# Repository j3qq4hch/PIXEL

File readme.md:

###PIXEL###
Pixel(yet another) is a dirt cheap 10W LED constant current driver with bells and whistles. 

Two common use scenarios are:

* LED LIGHTING with digital interface(smarthome applications)
* HUGE low-res LED screens with incredible brightness
 
 The device can operate in 2 modes:
 
* As modbus slave device over RS485 non-isolated inteface. This is relative slow mode which can be used for lighting automation systems or stage light control systems.  In this mode device's clock source is external quartz oscillator and it uses UART1 for communication. 
* As shift register. In this mode device operates like three daisy-chained 595 shift registers. In this mode device's clock source is internal RC(as frequency precision is not needed) and pins PF0 PF1 are used as GPIO(for LATCH and RESET signals). More, data clock is connected to PA4, data in is PA3, data out is PA9. So, data signal appears to be buffered by MCU. Clock, latch and reset signals are buffered by external ICs, so many PIXELs can be daisy-chained without concersn about bus integrity.  

Distinguishing between these modes is mostly a matter of proper connector selection, I think.  Mode selection may be done by adding solder joint to PA3 or PA9. These pins should be sampled right after MCU reset and one of the modes should be chosen then.

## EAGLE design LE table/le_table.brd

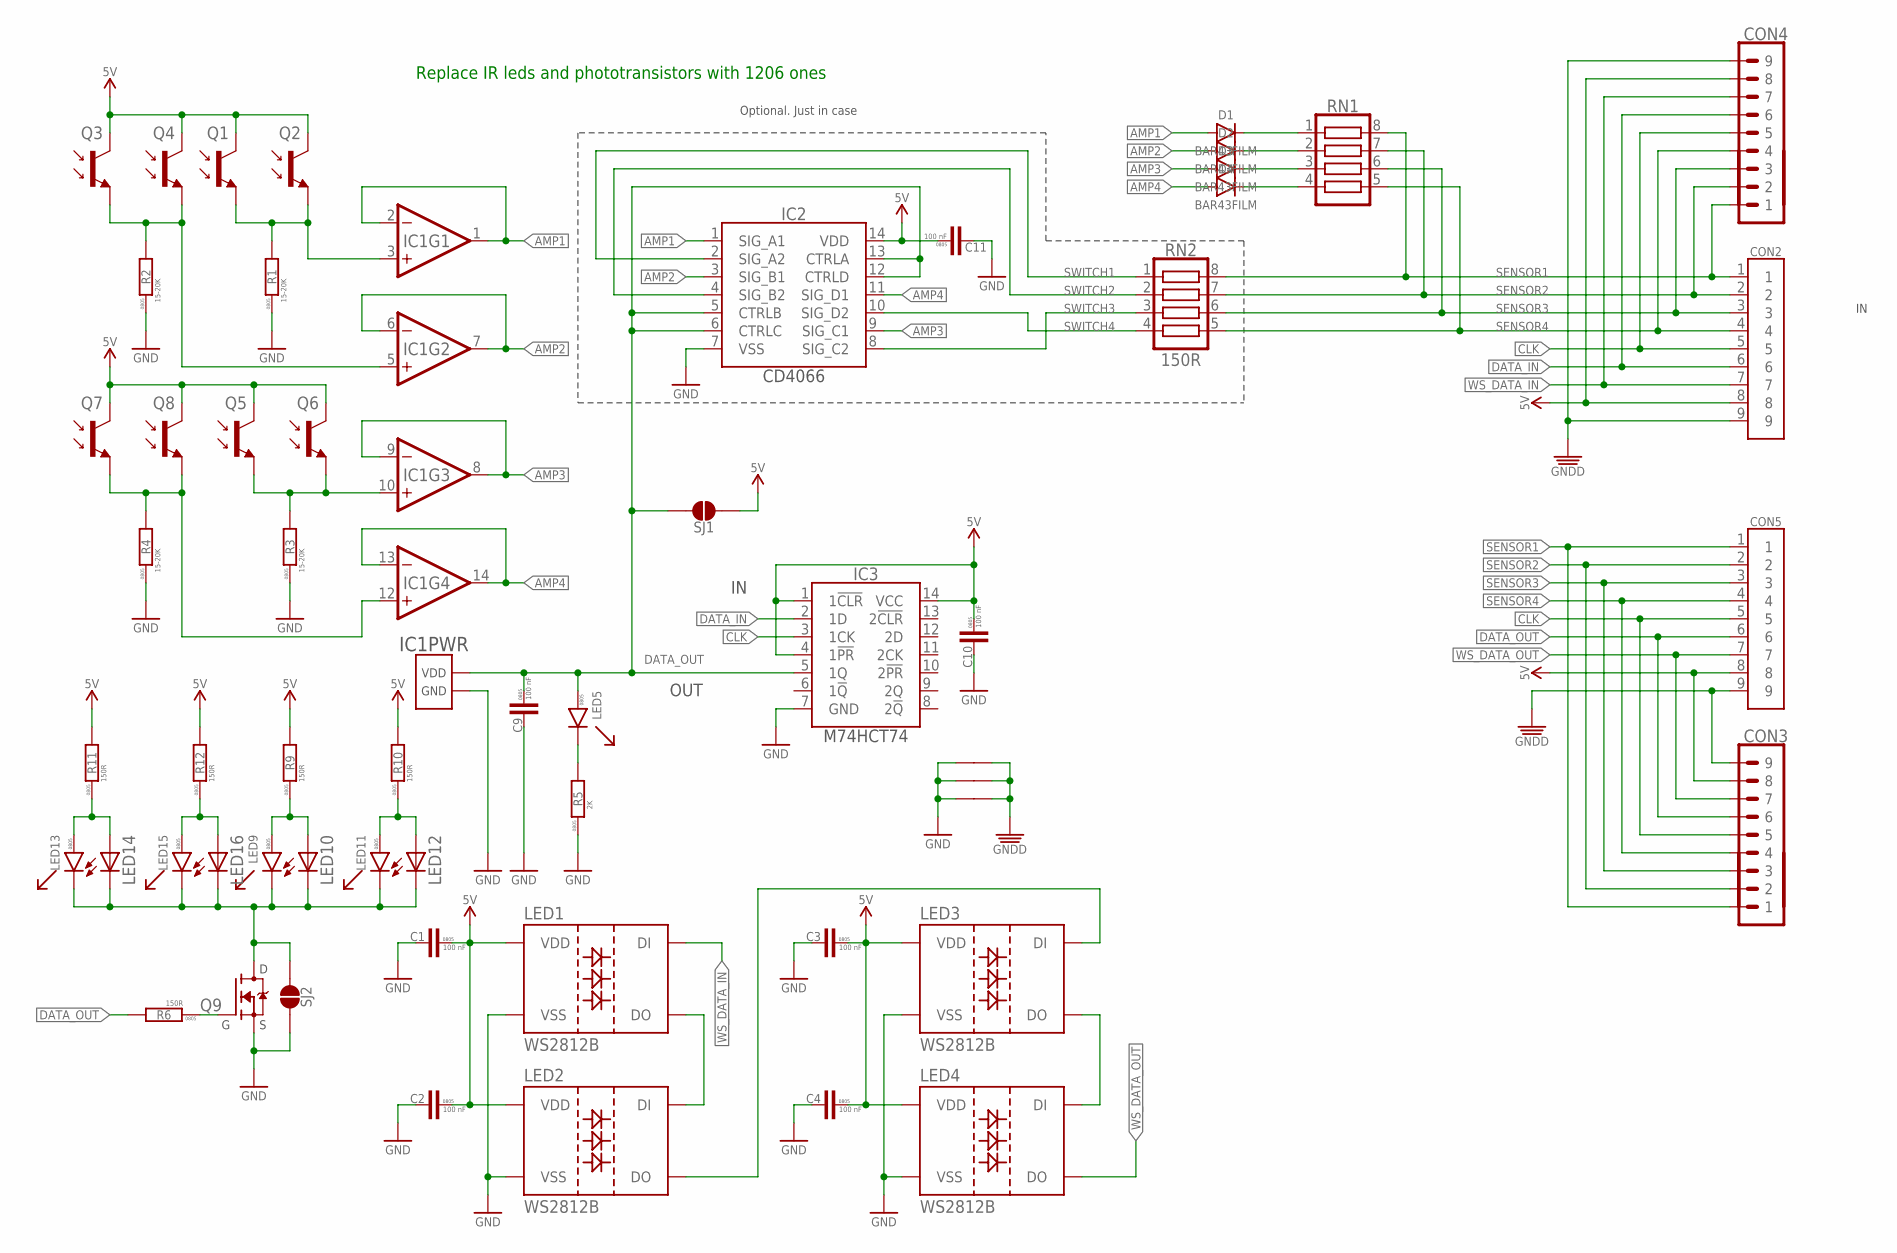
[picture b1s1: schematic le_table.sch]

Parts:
C1, C2, C3, C4, C9, C10, C11: 100 nF; C0805; FARNELL# 2496834
CON2, CON5: CONNECTOR
CON3, CON4: PINHEAD_1X09-2; 1X09-PTH_2
D1, D2, D3, D4: BAR43AFILM; SOT23-3
IC1: LM2902DT; SO-14
IC2: CD4066; SO-14
IC3: M74HCT74; SO-14
LED1, LED2, LED3, LED4: WS2812B
LED5, LED9, LED11, LED13, LED15: LED-0805; 0805_LED
LED10, LED12, LED14, LED16: LED-3MM
Q1, Q3, Q5, Q7: PHOTOTRANSISTOR-3MM; LED-3MM
Q2, Q4, Q6, Q8: PHOTOTRANSISTOR-0805; 0805
Q9: IRLML2502-SOT23; SOT23B-3
R1, R2, R3, R4: 15-20K; R0805
R5: 2K; R0805
R6, R9, R10, R11, R12: 150R; R0805
RN1: RESISTOR_ARRAY; CAT16-J4
RN2: 150R; CAT16-J4
SJ1, SJ2: SOLDER_JOINT; RES_0
U$3, U$6, U$7: CONNECTION

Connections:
AMP1: D1.1 (A), IC1.1 (OUT), IC1.2 (-IN), IC2.1 (SIG_A1)
AMP2: D2.1 (A), IC1.6 (-IN), IC1.7 (OUT), IC2.3 (SIG_B1)
AMP3: D3.1 (A), IC1.8 (OUT), IC1.9 (-IN), IC2.9 (SIG_C1)
AMP4: D4.1 (A), IC1.13 (-IN), IC1.14 (OUT), IC2.11 (SIG_D1)
CLK: CON2.5, CON3.5, CON4.5, CON5.5, IC3.3 (1CK)
DATA_IN: CON2.6, CON4.6, IC3.2 (1D)
DATA_OUT: C9.1, CON3.6, CON5.6, IC1.4 (VDD), IC2.5 (CTRLB), IC2.6 (CTRLC), IC2.12 (CTRLD), IC2.13 (CTRLA), IC3.5 (1Q), LED5.A, R6.2, SJ1.2
GND: C1.2, C2.2, C3.2, C4.2, C9.2, C10.2, C11.2, IC1.11 (GND), IC2.7 (VSS), IC3.7 (GND), LED1.3 (VSS), LED2.3 (VSS), LED3.3 (VSS), LED4.3 (VSS), Q9.2 (S), R1.1, R2.1, R3.1, R4.1, R5.1, SJ2.2, U$3.P$2, U$6.P$2, U$7.P$2
GNDD: CON2.9, CON3.9, CON4.9, CON5.9, U$3.P$1, U$6.P$1, U$7.P$1
unnamed: Q9.1 (G), R6.1
unnamed: LED5.C, R5.2
unnamed: LED1.2 (DO), LED2.4 (DI)
unnamed: LED2.2 (DO), LED3.4 (DI)
unnamed: LED3.2 (DO), LED4.4 (DI)
unnamed: LED11.A, LED12.A, R10.1
unnamed: LED13.A, LED14.A, R11.1
unnamed: LED9.A, LED10.A, R9.1
unnamed: LED15.A, LED16.A, R12.1
unnamed: D1.3 (C), RN1.1
unnamed: D2.3 (C), RN1.2
unnamed: D3.3 (C), RN1.3
unnamed: D4.3 (C), RN1.4
unnamed: LED9.C, LED10.K (C), LED11.C, LED12.K (C), LED13.C, LED14.K (C), LED15.C, LED16.K (C), Q9.3 (D), SJ2.1
SENS1: IC1.3 (+IN), Q1.K (E), Q2.2 (E), R1.2
SENS2: IC1.5 (+IN), Q3.K (E), Q4.2 (E), R2.2
SENS3: IC1.10 (+IN), Q5.K (E), Q6.2 (E), R3.2
SENS4: IC1.12 (+IN), Q7.K (E), Q8.2 (E), R4.2
SENSOR1: CON2.1, CON3.1, CON4.1, CON5.1, RN1.8, RN2.8
SENSOR2: CON2.2, CON3.2, CON4.2, CON5.2, RN1.7, RN2.7
SENSOR3: CON2.3, CON3.3, CON4.3, CON5.3, RN1.6, RN2.6
SENSOR4: CON2.4, CON3.4, CON4.4, CON5.4, RN1.5, RN2.5
SWITCH1: IC2.2 (SIG_A2), RN2.1
SWITCH2: IC2.4 (SIG_B2), RN2.2
SWITCH3: IC2.8 (SIG_C2), RN2.3
SWITCH4: IC2.10 (SIG_D2), RN2.4
VDD_5V: C1.1, C2.1, C3.1, C4.1, C10.1, C11.1, CON2.8, CON3.8, CON4.8, CON5.8, IC2.14 (VDD), IC3.1 (1!CLR), IC3.4 (1!PR), IC3.14 (VCC), LED1.1 (VDD), LED2.1 (VDD), LED3.1 (VDD), LED4.1 (VDD), Q1.A (C), Q2.1 (C), Q3.A (C), Q4.1 (C), Q5.A (C), Q6.1 (C), Q7.A (C), Q8.1 (C), R9.2, R10.2, R11.2, R12.2, SJ1.1
WS_DATA_IN: CON2.7, CON4.7, LED1.4 (DI)
WS_DATA_OUT: CON3.7, CON5.7, LED4.2 (DO)

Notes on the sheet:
OUT
Optional. Just in case
Replace IR leds and phototransistors with 1206 ones

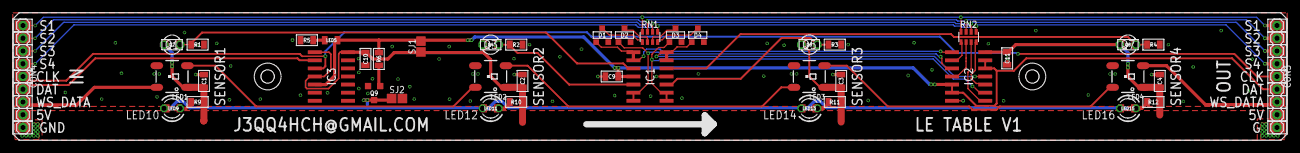
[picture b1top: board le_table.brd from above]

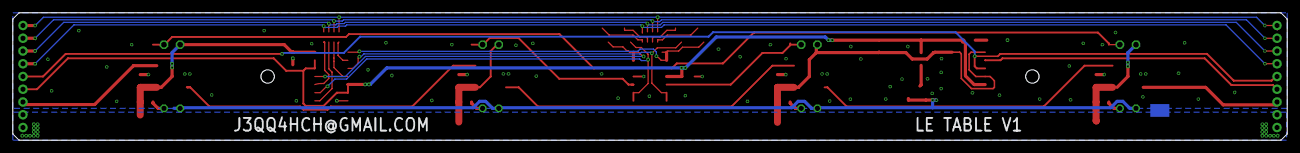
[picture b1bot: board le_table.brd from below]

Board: 2 copper layers, 200.0 x 20.0 mm, 59 parts (3 on the bottom side), 38 nets.

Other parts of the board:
U$1, U$4: MOUNTING_HOLE_M2

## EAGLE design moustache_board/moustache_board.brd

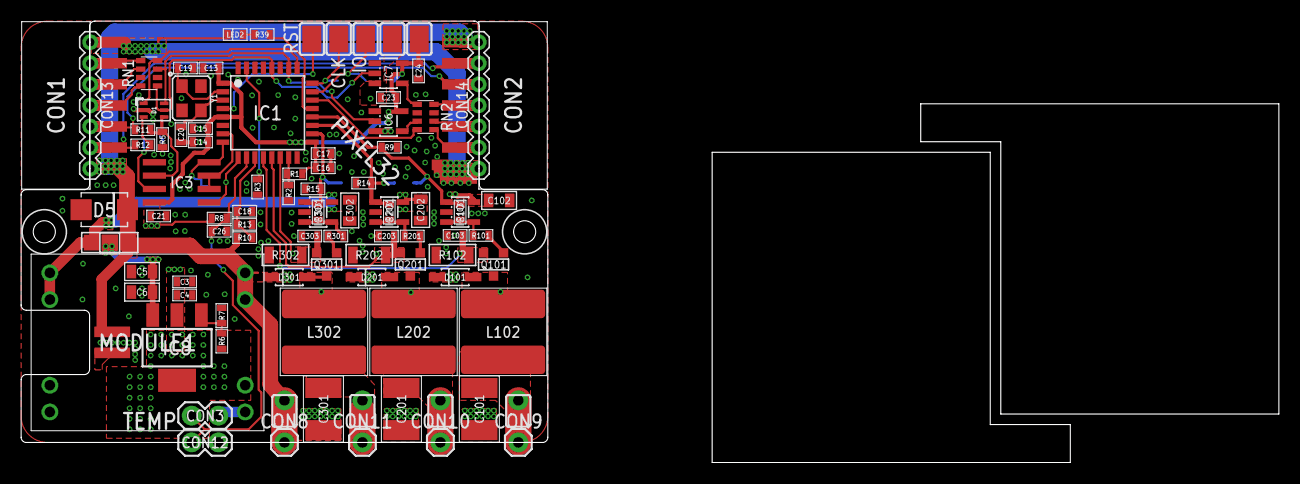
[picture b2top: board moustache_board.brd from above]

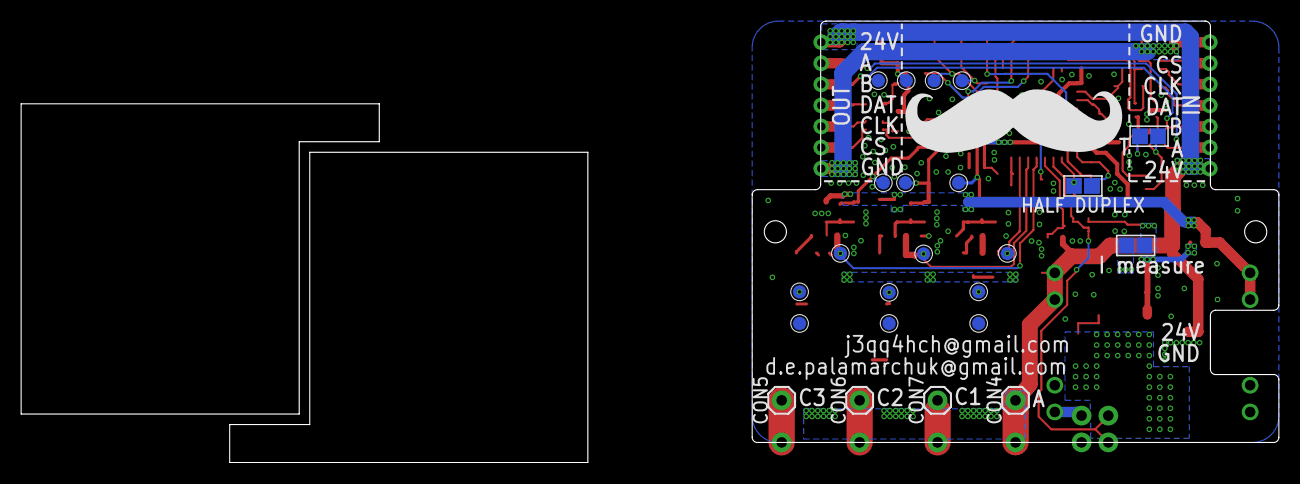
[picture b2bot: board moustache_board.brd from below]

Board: 2 copper layers, 50.0 x 40.0 mm, 129 parts (24 on the bottom side), 57 nets.

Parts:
C3, C4, C16: 4.7 uF; C0603
C5, C6: 100 nF; C0805
C13, C17, C18, C21, C23, C24, C26, C103, C203, C303: 100 nF; C0603
C14: 1 uF; C0603
C15: 10 nF; C0603
C19, C20: 10 pF; C0603
C101, C201, C301: 10 uF; C1812
C102, C202, C302: 1 uF; C0805
CON1, CON2: B7B-PH-K-S-SIDE; B7B-PH-K-S_SIDE
CON3, CON12: PINHEAD_1X02-2.54; 1X02-PTH-2.54
CON4, CON5, CON6, CON7, CON8, CON9, CON10, CON11: PINHEAD_1X01-2.54; 1X01-PTH-2.54
CON13, CON14: PINHEAD_1X07-2; 1X07-PTH-2
CON15: B2B-PH-K-S_SIDE_MOUNT
D1: SMF05C; SC70_6L
D5: TVS_DIODE-SMB; SMB
D101, D201, D301: DIODE-SOD123; SOD123
DRILEGEND: DRILEGEND
IC1: STM32F030K6TX-LQFP32(7X7); LQFP32-7X7
IC3: ST3485SOIC8; SOIC8
IC6, IC7: MC74VHC1GT125; SOT23-5
IC8: LM317; SOT223
IC101, IC201, IC301: IRS44273L; SOT23-5
L102, L202, L302: 47UH; SDR0805
LED2: LED-0603; LED0603
LED_ANODE: WIREPADSMD2.5-1.8; PAD-2.5-1.8
LED_CATHODE1, LED_CATHODE2, LED_CATHODE3: WIREPADSMD2.5-1.8; PAD-2.5-1.8
MODULE1: GW1584
PAD1, PAD2, PAD3, PAD4, PAD5: WIREPADSMD2.5-1.8; PAD-2.5-1.8
Q101, Q201, Q301: N-FET-SOT23; SOT23-3
R1, R2, R11, R12: 100R; R0603
R3, R8, R9, R13, R14, R15: 10K; R0603
R5: 120R; R0603
R6, R39: 1K; R0603
R7: 1K6; R0603
R10: 100K; R0603
R101, R103, R201, R203, R301, R303: 22R; R0603
R102, R202, R302: 2R; R1206
RN1, RN2: 510R; CAT16-J4
SJ1, SJ2, SJ3, SJ4, SJ5: RES_0
TP1, TP2, TP3, TP4, TP101, TP102, TP103, TP104, TP201, TP202, TP203, TP204, TP301, TP302, TP303, TP304: PAD.05; PAD.05X.05
U$2: BOARD_OUTLINE
U$3, U$6, U$7, U$8, U$9, U$10: CONNECTION
U$4, U$5: MOUNTING_HOLE_M2
U$11: MOUSTACHE2
Y1: 16MHz; OSCILLATOR-3.2X2.5

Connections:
A: D1.4, IC3.6, R5.2, R11.1
B: D1.3, IC3.7, R12.1, SJ2.1
CLOCK: D1.6, IC1.26, IC6.2, RN1.3
CLOCK_BUFFERED: IC6.4, RN2.3
CS: D1.1, IC1.25, RN1.4
CS_OUT: IC1.22, RN2.4
DATA_BUFFERED: IC7.4, RN2.1
GND: C3.1, C4.1, C5.1, C6.1, C13.1, C14.1, C15.1, C16.1, C17.1, C18.1, C19.2, C20.2, C21.1, C23.1, C24.1, C26.1, C102.1, C103.1, C202.1, C203.1, C302.1, C303.1, CON3.1, CON12.1, CON15.1, D1.2, D5.A, IC1.16, IC1.32, IC3.5, IC6.3, IC7.3, IC101.2, IC201.2, IC301.2, MODULE1.IN-@1, MODULE1.IN-@2, MODULE1.OUT-@1, MODULE1.OUT-@2, PAD4.P$1, R2.2, R3.2, R7.1, R9.1, R13.1, R14.1, R15.1, R102.P$1, R202.P$1, R302.P$1, TP2.P$1, TP104.P$1, TP204.P$1, TP304.P$1, U$3.P$2, U$6.P$2, U$7.P$2, U$8.P$2, U$9.P$2, U$10.P$2, Y1.2, Y1.4
GNDD: CON1.7, CON2.7, CON13.1, CON14.1, LED2.C, U$3.P$1, U$6.P$1, U$7.P$1, U$8.P$1, U$9.P$1, U$10.P$1
LED1_CURRENT: C103.2, IC1.12, Q101.2, R102.P$2, TP103.P$1
LED1_PWM: IC1.20, IC101.1, R9.2, R103.1, TP101.P$1
LED2_CURRENT: C203.2, IC1.13, Q201.2, R202.P$2, TP203.P$1
LED2_PWM: IC1.19, IC201.1, R14.2, R203.1, TP201.P$1
LED3_CURRENT: C303.2, IC1.14, Q301.2, R302.P$2, TP303.P$1
LED3_PWM: IC1.18, IC301.1, R15.2, R303.1, TP301.P$1
LED_DRIVER1:N$2: D101.A, L102.1, Q101.3, TP102.P$1
LED_DRIVER1:N$3: IC101.3, IC101.4, R101.1, R103.2
LED_DRIVER1:N$7: Q101.1, R101.2
LED_DRIVER2:N$2: D201.A, L202.1, Q201.3, TP202.P$1
LED_DRIVER2:N$3: IC201.3, IC201.4, R201.1, R203.2
LED_DRIVER2:N$7: Q201.1, R201.2
LED_DRIVER3:N$2: D301.A, L302.1, Q301.3, TP302.P$1
LED_DRIVER3:N$3: IC301.3, IC301.4, R301.1, R303.2
LED_DRIVER3:N$7: Q301.1, R301.2
MOSI/DATA: D1.5, IC1.28, IC7.2, RN1.1
unnamed: R5.1, SJ2.2
unnamed: C3.2, C4.2, IC8.2, IC8.4, R6.2, SJ4.2
unnamed: IC1.15, R1.1, R2.1
unnamed: C19.1, IC1.2, Y1.1
unnamed: C5.2, C6.2, IC8.3, SJ1.2, SJ3.2
unnamed: IC1.31, R3.1
unnamed: C20.1, IC1.3, Y1.3
unnamed: C101.P$1, CON5.1, CON9.1, L102.2, LED_CATHODE1.P$1
unnamed: CON1.4, CON13.4, RN1.8
unnamed: CON1.5, CON13.3, RN1.6
unnamed: CON1.6, CON13.2, RN1.5
unnamed: CON2.4, CON14.4, RN2.8
unnamed: CON2.5, CON14.3, RN2.6
unnamed: CON2.6, CON14.2, RN2.5
unnamed: IC8.1, R6.1, R7.2
unnamed: C201.P$1, CON6.1, CON10.1, L202.2, LED_CATHODE2.P$1
unnamed: LED2.A, R39.1
unnamed: C301.P$1, CON7.1, CON11.1, L302.2, LED_CATHODE3.P$1
RE/DE: IC1.7, IC3.2, IC3.3
RS485_A: CON1.2, CON2.2, CON13.6, CON14.6, R12.2
RS485_B: CON1.3, CON2.3, CON13.5, CON14.5, R11.2
RST: IC1.4, PAD5.P$1
RX: IC1.9, IC3.1, SJ5.2
STAT_LED: IC1.21, R39.2
SWCLK: IC1.24, PAD1.P$1, TP4.P$1
SWIO: IC1.23, PAD2.P$1, TP1.P$1
TEMP: C26.2, CON3.2, CON12.2, IC1.10, R8.1
TX: IC1.8, IC3.4, SJ5.1
VDD_3V3: C13.2, C14.2, C15.2, C16.2, C17.2, C21.2, C23.2, C24.2, IC1.1, IC1.5, IC1.17, IC3.8, IC6.5, IC7.5, PAD3.P$1, R1.2, R8.2, SJ4.1, TP3.P$1
VDD_12V: C102.2, C202.2, C302.2, IC101.5, IC201.5, IC301.5, MODULE1.OUT+@1, MODULE1.OUT+@2, SJ1.1
VDD_24V: C101.P$2, C201.P$2, C301.P$2, CON1.1, CON2.1, CON4.1, CON8.1, CON13.7, CON14.7, CON15.2, D5.C, D101.C, D201.C, D301.C, LED_ANODE.P$1, MODULE1.IN+@1, MODULE1.IN+@2, R10.1, SJ3.1
VIN_SENSE: C18.2, IC1.11, R10.2, R13.2

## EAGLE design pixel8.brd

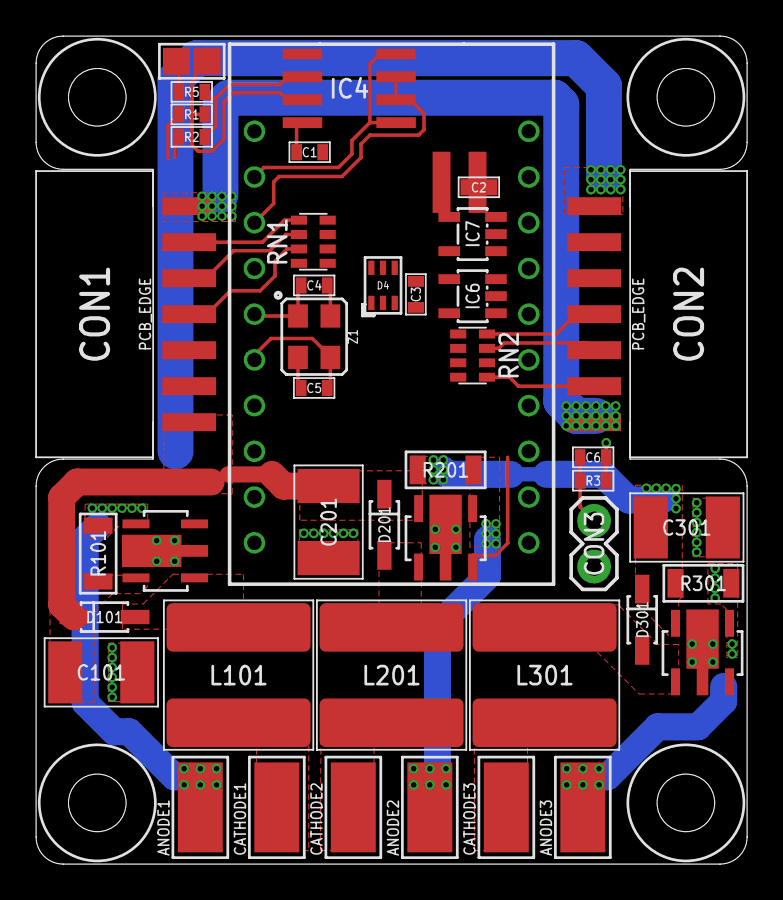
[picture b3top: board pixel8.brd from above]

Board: 2 copper layers, 39.5 x 46.0 mm, 50 parts (1 on the bottom side), 38 nets.

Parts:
ANODE1, ANODE2, ANODE3: WIREPADSMD5-2,5; 5-2,5
C1: 0.1uF; C0603
C2, C3, C6: 100 nF; C0603
C4, C5: C0603
C101, C201, C301: 10 uF; C1812
CATHODE1, CATHODE2, CATHODE3: WIREPADSMD5-2,5; 5-2,5
CON1, CON2: DS1066-07M-SIDE; DS1066-08M_SIDE
CON3: PINHEAD_1X02-2.54; 1X02-PTH-2.54
CON15: B2B-PH-K-S_SIDE_MOUNT
D4: SMF05C; SC70_6L
D101, D201, D301: CRS08-SOD123; SOD123
IC4: ST3485SOIC8; SOIC8
IC6, IC7: MC74VHC1GT125; SOT23-5
IC101, IC201, IC301: PT4115
L101, L201, L301: 47UH; SDR0805
MODULE1: STM8S_MIN_DEV_BOARD; STM8_MIN_DEV_BOARD
R1, R2: 100R; R0603
R3: 10K; R0603
R5: 120R; R0603
R101, R201, R301: R1206
RN1, RN2: 510R; CAT16-J4
SJ2: RES_0
U$1: PIXEL8_BOARD_OUTLINE
U$2, U$3, U$4, U$5: MOUNTING_HOLE_M3
U$6: CONNECTION
Z1: 16MHz; OSCILLATOR-3.2X2.5

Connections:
A: D4.4, IC4.6, R2.1, R5.2
A1: ANODE1.1, IC101.4, R101.P$1
A2: ANODE2.1, IC201.4, R201.P$1
A3: ANODE3.1, IC301.4, R301.P$1
B: D4.3, IC4.7, R1.1, SJ2.1
C1: CATHODE1.1, L101.2
C2: CATHODE2.1, L201.2
C3: CATHODE3.1, L301.2
CLOCK: D4.6, IC6.2, MODULE1.15, RN1.3
CLOCK_BUFFERED: IC6.4, RN2.2
CS: D4.1, MODULE1.10, RN1.4
CS_OUT: MODULE1.13, RN2.4
DATA_BUFFERED: IC7.4, RN2.1
GND: C1.1, C2.1, C3.1, C4.2, C5.2, C6.1, C101.P$1, C201.P$1, C301.P$1, CON15.1, D4.2, IC4.5, IC6.3, IC7.3, IC101.2, IC101.2A, IC201.2, IC201.2A, IC301.2, IC301.2A, MODULE1.7, R3.1, U$6.P$2, Z1.2, Z1.4
GNDD: CON1.7, CON2.7, U$6.P$1
LED_DRV1:SW: D101.A, IC101.1, L101.1
LED_DRV2:SW: D201.A, IC201.1, L201.1
LED_DRV3:SW: D301.A, IC301.1, L301.1
MOSI/DATA: D4.5, IC7.2, MODULE1.16, RN1.2
unnamed: CON2.4, RN2.8
unnamed: CON2.6, RN2.5
unnamed: R5.1, SJ2.2
unnamed: C4.1, MODULE1.5, Z1.1
unnamed: C5.1, MODULE1.6, Z1.3
unnamed: CON1.4, RN1.7
unnamed: CON1.5, RN1.6
unnamed: CON1.6, RN1.5
unnamed: CON2.5, RN2.7
PWM1: IC101.3, MODULE1.1
PWM2: IC201.3, MODULE1.20
PWM3: IC301.3, MODULE1.19
RE/DE: IC4.2, IC4.3, MODULE1.3
RS485_A: CON1.2, CON2.2, R1.2
RS485_B: CON1.3, CON2.3, R2.2
RX/TX: IC4.1, IC4.4, MODULE1.2
TEMP: C6.2, CON3.1, MODULE1.14, R3.2
VDD_3V3: C1.2, C2.2, C3.2, CON3.2, IC4.8, IC6.5, IC7.5, MODULE1.9
VDD_12V: C101.P$2, C201.P$2, C301.P$2, CON1.1, CON2.1, D101.C, D201.C, D301.C, IC101.5, IC201.5, IC301.5, R101.P$2, R201.P$2, R301.P$2

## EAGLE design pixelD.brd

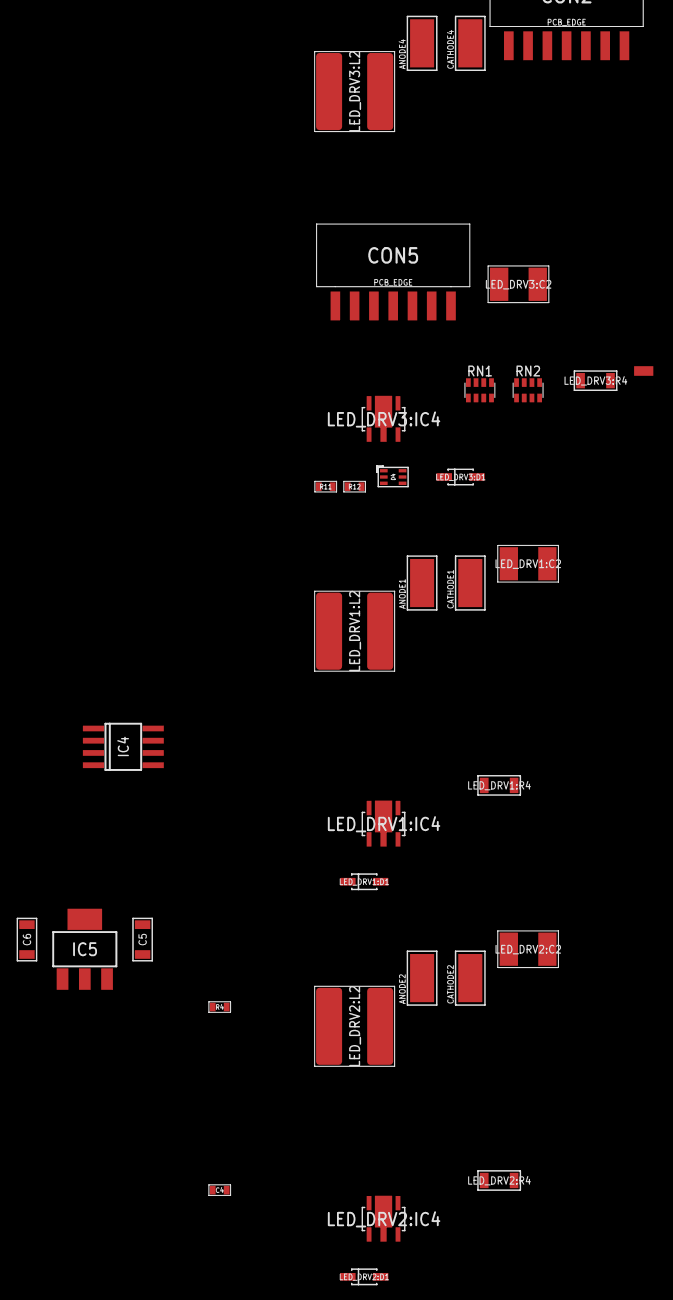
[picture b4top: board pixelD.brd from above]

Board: 2 copper layers, 36 parts (1 on the bottom side), 32 nets, no tracks yet.

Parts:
ANODE1, ANODE2, ANODE4: WIREPADSMD5-2,5; 5-2,5
C4: C0603
C5, C6: C1206
CATHODE1, CATHODE2, CATHODE4: WIREPADSMD5-2,5; 5-2,5
CON2, CON5: DS1066-07M-SIDE; DS1066-08M_SIDE
D4: SMF05C; SC70_6L
IC4: WS2811; SOIC8
IC5: LM1117-3.3-SOT223; SOT223
LED_DRV1:C2, LED_DRV2:C2, LED_DRV3:C2: 10 uF; C1812
LED_DRV1:D1, LED_DRV2:D1, LED_DRV3:D1: CRS08-SOD123; SOD123
LED_DRV1:IC4, LED_DRV2:IC4, LED_DRV3:IC4: PT4115
LED_DRV1:L2, LED_DRV2:L2, LED_DRV3:L2: 47UH; SDR0805
LED_DRV1:R4, LED_DRV2:R4, LED_DRV3:R4: R1206
R4, R11, R12: 100R; R0603
R6: RES_0
RN1, RN2: 510R; CAT16-J4
U$6: CONNECTION

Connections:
A: D4.4, R11.1
B: D4.3, R12.1
CLOCK: D4.6, RN1.3
CS: D4.1, RN1.4
GND: C4.2, C5.P$1, C6.P$1, D4.2, IC4.4, IC5.1, LED_DRV1:C2.P$1, LED_DRV1:IC4.2, LED_DRV1:IC4.2A, LED_DRV2:C2.P$1, LED_DRV2:IC4.2, LED_DRV2:IC4.2A, LED_DRV3:C2.P$1, LED_DRV3:IC4.2, LED_DRV3:IC4.2A, U$6.P$2
GNDD: CON2.7, CON5.7, U$6.P$1
LED_DRV1:N$2: LED_DRV1:D1.A, LED_DRV1:IC4.1, LED_DRV1:L2.1
LED_DRV2:N$2: LED_DRV2:D1.A, LED_DRV2:IC4.1, LED_DRV2:L2.1
LED_DRV3:N$2: LED_DRV3:D1.A, LED_DRV3:IC4.1, LED_DRV3:L2.1
MOSI/DATA: D4.5, RN1.2
unnamed: IC4.7, R6.2
unnamed: CATHODE1.1, LED_DRV1:L2.2
unnamed: C4.1, IC4.8, R4.1
unnamed: ANODE1.1, LED_DRV1:IC4.4, LED_DRV1:R4.P$1
unnamed: CATHODE2.1, LED_DRV2:L2.2
unnamed: CON2.4, RN1.7
unnamed: ANODE2.1, LED_DRV2:IC4.4, LED_DRV2:R4.P$1
unnamed: CON2.5, RN1.6
unnamed: CON5.4, RN2.8
unnamed: CON5.6, RN2.5
unnamed: CON5.5, RN2.7
unnamed: CON2.6, RN1.5
unnamed: CATHODE4.1, LED_DRV3:L2.2
unnamed: ANODE4.1, LED_DRV3:IC4.4, LED_DRV3:R4.P$1
PWM1: IC4.1, LED_DRV3:IC4.3
PWM2: IC4.2, LED_DRV1:IC4.3
PWM_B: IC4.3, LED_DRV2:IC4.3
RS485_A1: CON2.2, CON5.2, R12.2
RS485_B1: CON2.3, CON5.3, R11.2
VDD_5V: C6.P$2, IC5.2, IC5.4, R4.2, R6.1
VDD_12V: C5.P$2, IC5.3
VDD_24V: CON2.1, CON5.1, LED_DRV1:C2.P$2, LED_DRV1:D1.C, LED_DRV1:IC4.5, LED_DRV1:R4.P$2, LED_DRV2:C2.P$2, LED_DRV2:D1.C, LED_DRV2:IC4.5, LED_DRV2:R4.P$2, LED_DRV3:C2.P$2, LED_DRV3:D1.C, LED_DRV3:IC4.5, LED_DRV3:R4.P$2

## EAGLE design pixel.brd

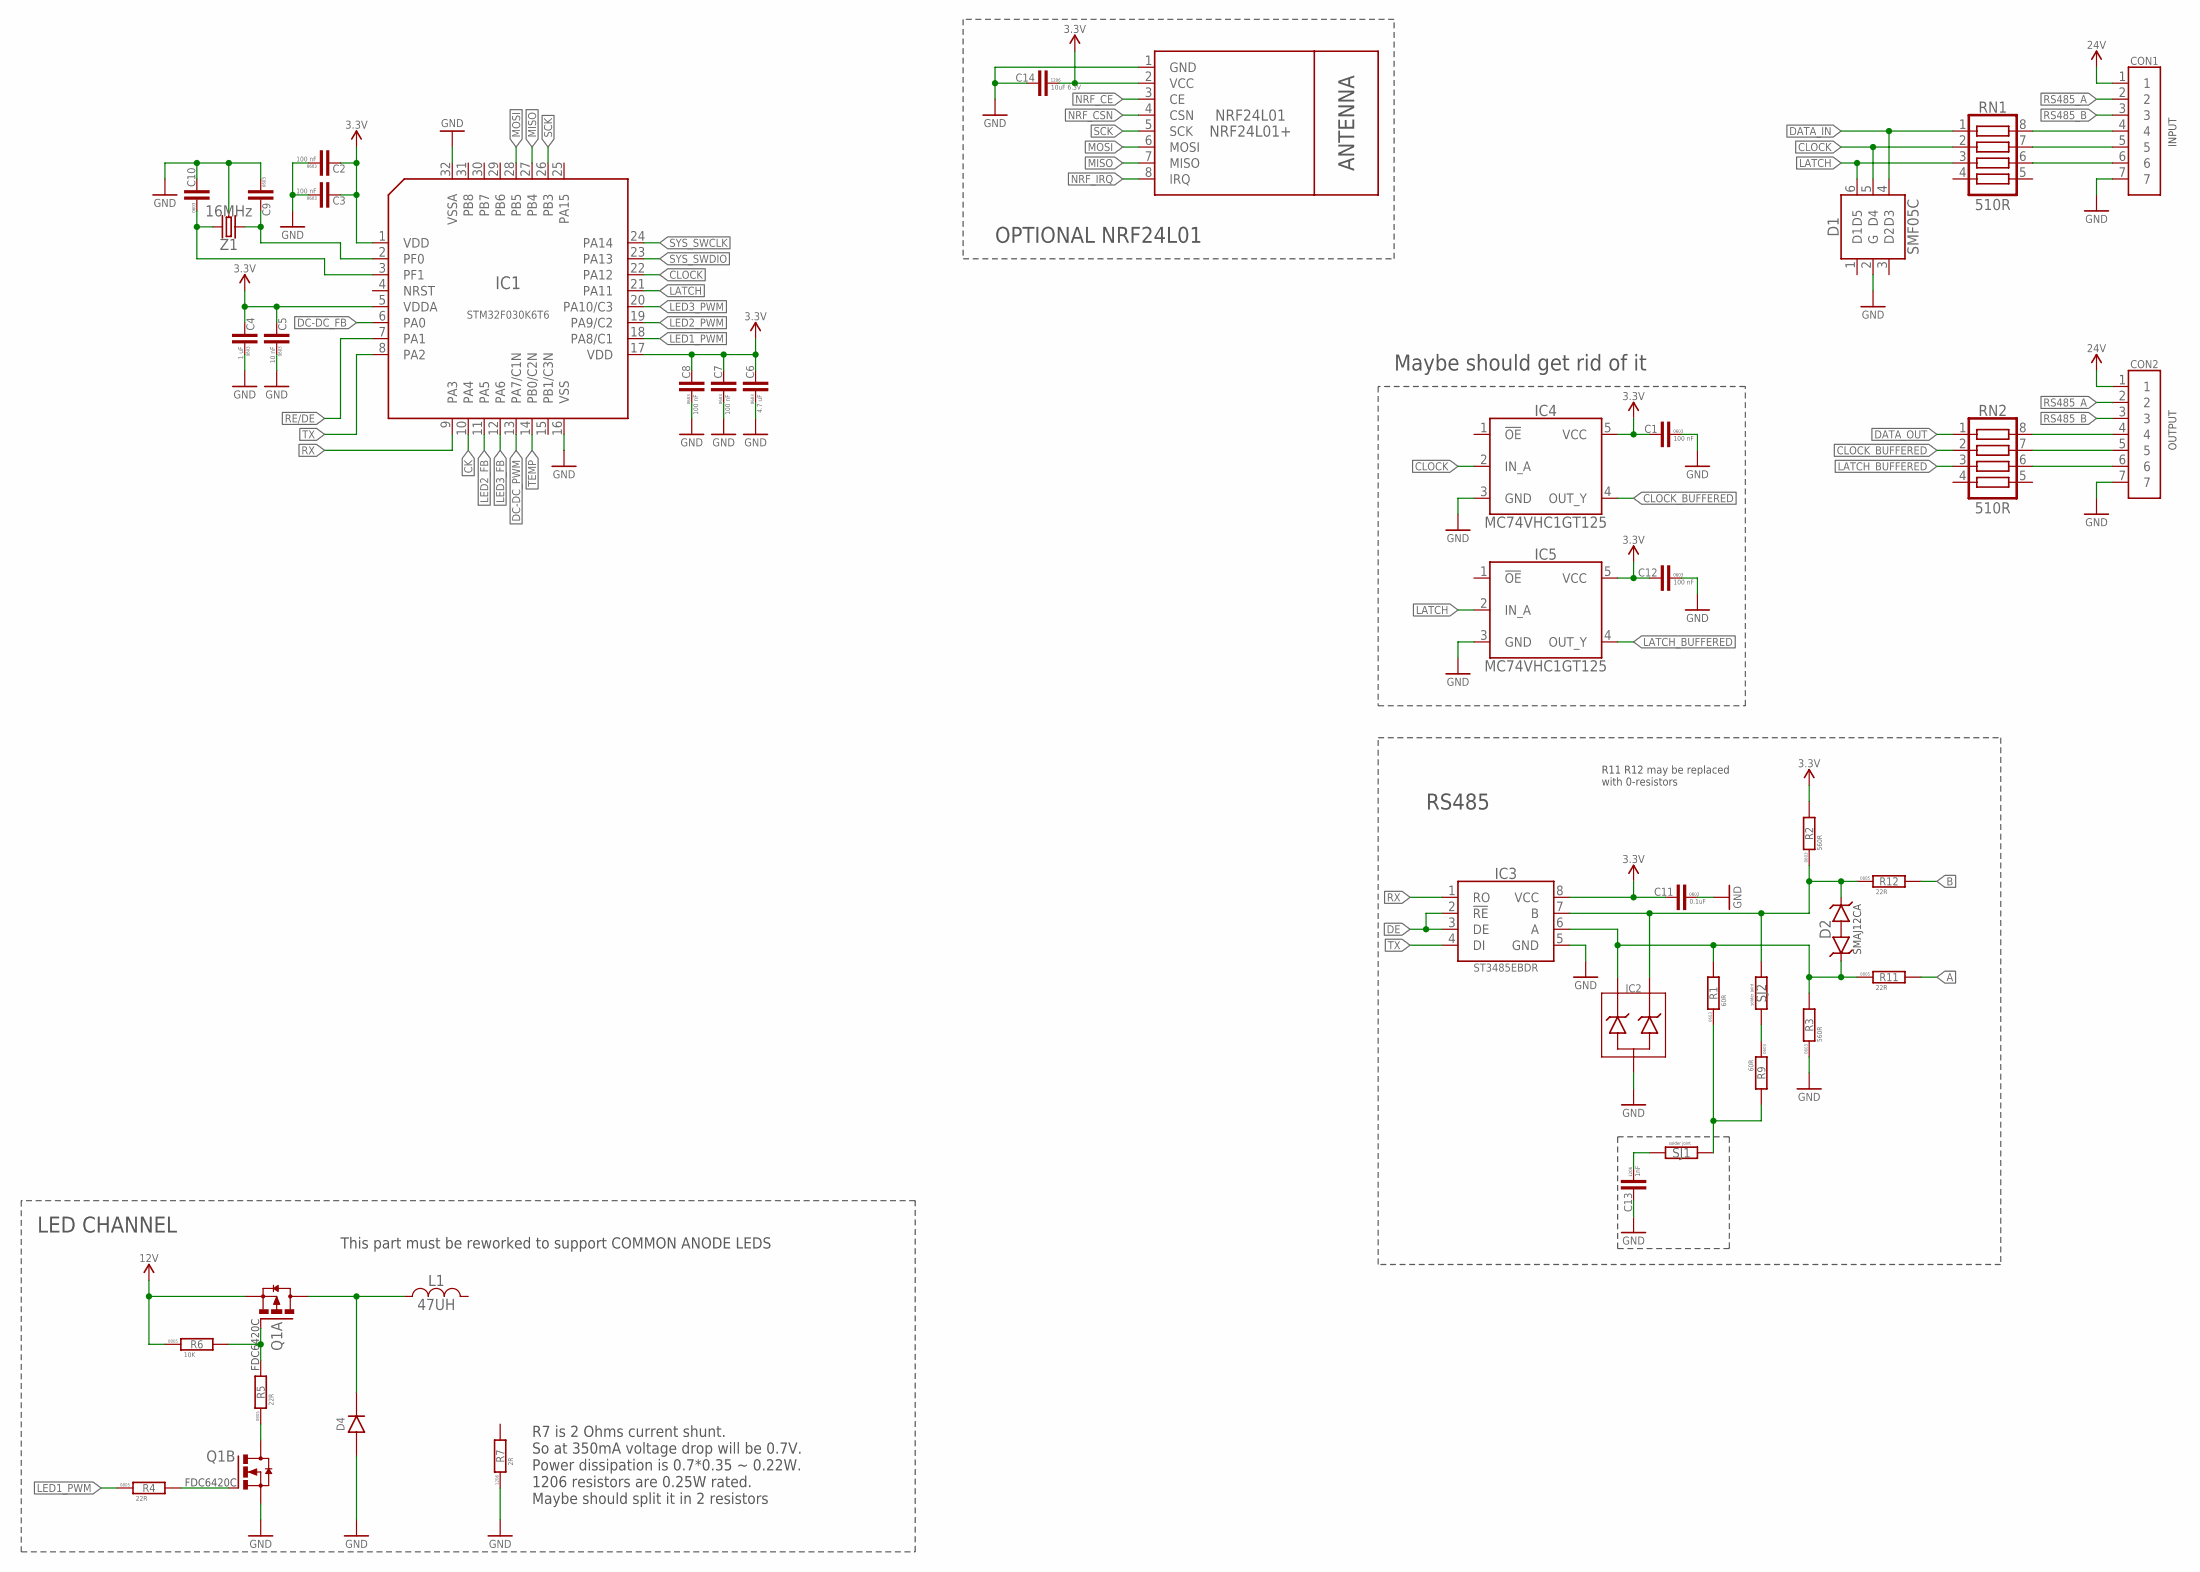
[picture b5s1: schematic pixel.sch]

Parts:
C1, C2, C3, C7, C8, C12: 100 nF; C0603
C4: 1 uF; C0603
C5: 10 nF; C0603
C6: 4.7 uF; C0603
C9, C10: C-0603; C0603
C11: 0.1uF; C0603
C13: 1nF; C1206
C14: 10uF 6.3V; C1206
CON1, CON2: DS1066-07M-SIDE; DS1066-08M_SIDE
D1: SMF05C; SC70_6L
D2: SMAJ12A; SMA
D4: CRS08-SOD123; SOD123
IC1: STM32F030K6TX-LQFP32(7X7); LQFP32-7X7
IC2: ESDA6V1L; SOT23
IC3: ST3485SOIC8; SOIC8
IC4, IC5: MC74VHC1GT125; SOT23-5
L1: 47UH; SDR0604
NRF24L01: NRF24L01
Q1: FDC6420C; SOT23-6
R1, R9: 60R; R0603
R2, R3: 560R; R0603
R4, R5, R11, R12: 22R; R0805
R6: 10K; R0805
R7: 2R; R1206
RN1, RN2: 510R; CAT16-J4; DIGIKEY# CAT16-511J4LF-ND
SJ1, SJ2: SOLDER_JOINT; RES_0
Z1: 16MHz; OSCILLATOR-3.2X2.5

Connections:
A: D2.A, IC2.2 (C1), IC3.6 (A), R1.2, R3.2, R11.1, R11.2
B: D2.C, IC2.3 (C2), IC3.7 (B), R2.1, R12.1, R12.2, SJ2.1
CK: IC1.10 (PA4)
CLOCK: D1.5 (D4), IC1.22 (PA12), IC4.2 (IN_A), RN1.2
CLOCK_BUFFERED: IC4.4 (OUT_Y), RN2.2
DATA_IN: D1.4 (D3), RN1.1
DATA_OUT: RN2.1
DC-DC_FB: IC1.6 (PA0)
DC-DC_PWM: IC1.13 (PA7/C1N)
DE: IC3.2 (!RE), IC3.3 (DE)
GND: C1.1, C2.1, C3.1, C4.1, C5.1, C6.1, C7.1, C8.1, C9.1, C10.2, C11.1, C12.1, C13.P$2 (2), C14.P$2 (2), CON1.7, CON2.7, D1.2 (G), D4.A, IC1.16 (VSS), IC1.32 (VSSA), IC2.1 (A), IC3.5 (GND), IC4.3 (GND), IC5.3 (GND), NRF24L01.1 (GND), Q1.5 (S), R3.1, R7.P$1 (1), Z1.2 (GND), Z1.4 (GND)
LATCH: D1.6 (D5), IC1.21 (PA11), IC5.2 (IN_A), RN1.3
LATCH_BUFFERED: IC5.4 (OUT_Y), RN2.3
LED1_PWM: IC1.18 (PA8/C1), R4.1
LED2_FB: IC1.11 (PA5)
LED2_PWM: IC1.19 (PA9/C2)
LED3_FB: IC1.12 (PA6)
LED3_PWM: IC1.20 (PA10/C3)
MISO: IC1.27 (PB4), NRF24L01.7 (MISO)
MOSI: IC1.28 (PB5), NRF24L01.6 (MOSI)
unnamed: C9.2, IC1.2 (PF0), Z1.1
unnamed: CON1.4, RN1.8
unnamed: C10.1, IC1.3 (PF1), Z1.3 (2)
unnamed: CON1.5, RN1.7
unnamed: CON1.6, RN1.6
unnamed: CON2.4, RN2.8
unnamed: Q1.3 (G), R5.2, R6.2
unnamed: R1.1, R9.2, SJ1.1
unnamed: CON2.5, RN2.7
unnamed: R9.1, SJ2.2
unnamed: C13.P$1 (1), SJ1.2
unnamed: CON2.6, RN2.6
unnamed: Q1.1 (G), R4.2
unnamed: Q1.6 (D), R5.1
unnamed: D4.C, L1.1, Q1.2 (D)
NRF_CE: NRF24L01.3 (CE)
NRF_CSN: NRF24L01.4 (CSN)
NRF_IRQ: NRF24L01.8 (IRQ)
RE/DE: IC1.7 (PA1)
RS485_A: CON1.2, CON2.2
RS485_B: CON1.3, CON2.3
RX: IC1.9 (PA3), IC3.1 (RO)
SCK: IC1.26 (PB3), NRF24L01.5 (SCK)
SYS_SWCLK: IC1.24 (PA14)
SYS_SWDIO: IC1.23 (PA13)
TEMP: IC1.14 (PB0/C2N)
TX: IC1.8 (PA2), IC3.4 (DI)
VDD_3V3: C1.2, C2.2, C3.2, C4.2, C5.2, C6.2, C7.2, C8.2, C11.2, C12.2, C14.P$1 (1), IC1.1 (VDD), IC1.5 (VDDA), IC1.17 (VDD), IC3.8 (VCC), IC4.5 (VCC), IC5.5 (VCC), NRF24L01.2 (VCC), R2.2
VDD_12V: Q1.4 (S), R6.1
VDD_24V: CON1.1, CON2.1

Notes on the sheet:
INPUT
OUTPUT
RS485
R11 R12 may be replaced with 0-resistors
Maybe should get rid of it
LED CHANNEL
R7 is 2 Ohms current shunt. So at 350mA voltage drop will be 0.7V. Power dissipation is 0.7*0.35 ~ 0.22W. 1206 resistors are 0.25W rated. Maybe should split it in 2 resistors
This part must be reworked to support COMMON ANODE LEDS
OPTIONAL NRF24L01

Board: 2 copper layers, 42 parts (0 on the bottom side), 35 nets, no tracks yet.

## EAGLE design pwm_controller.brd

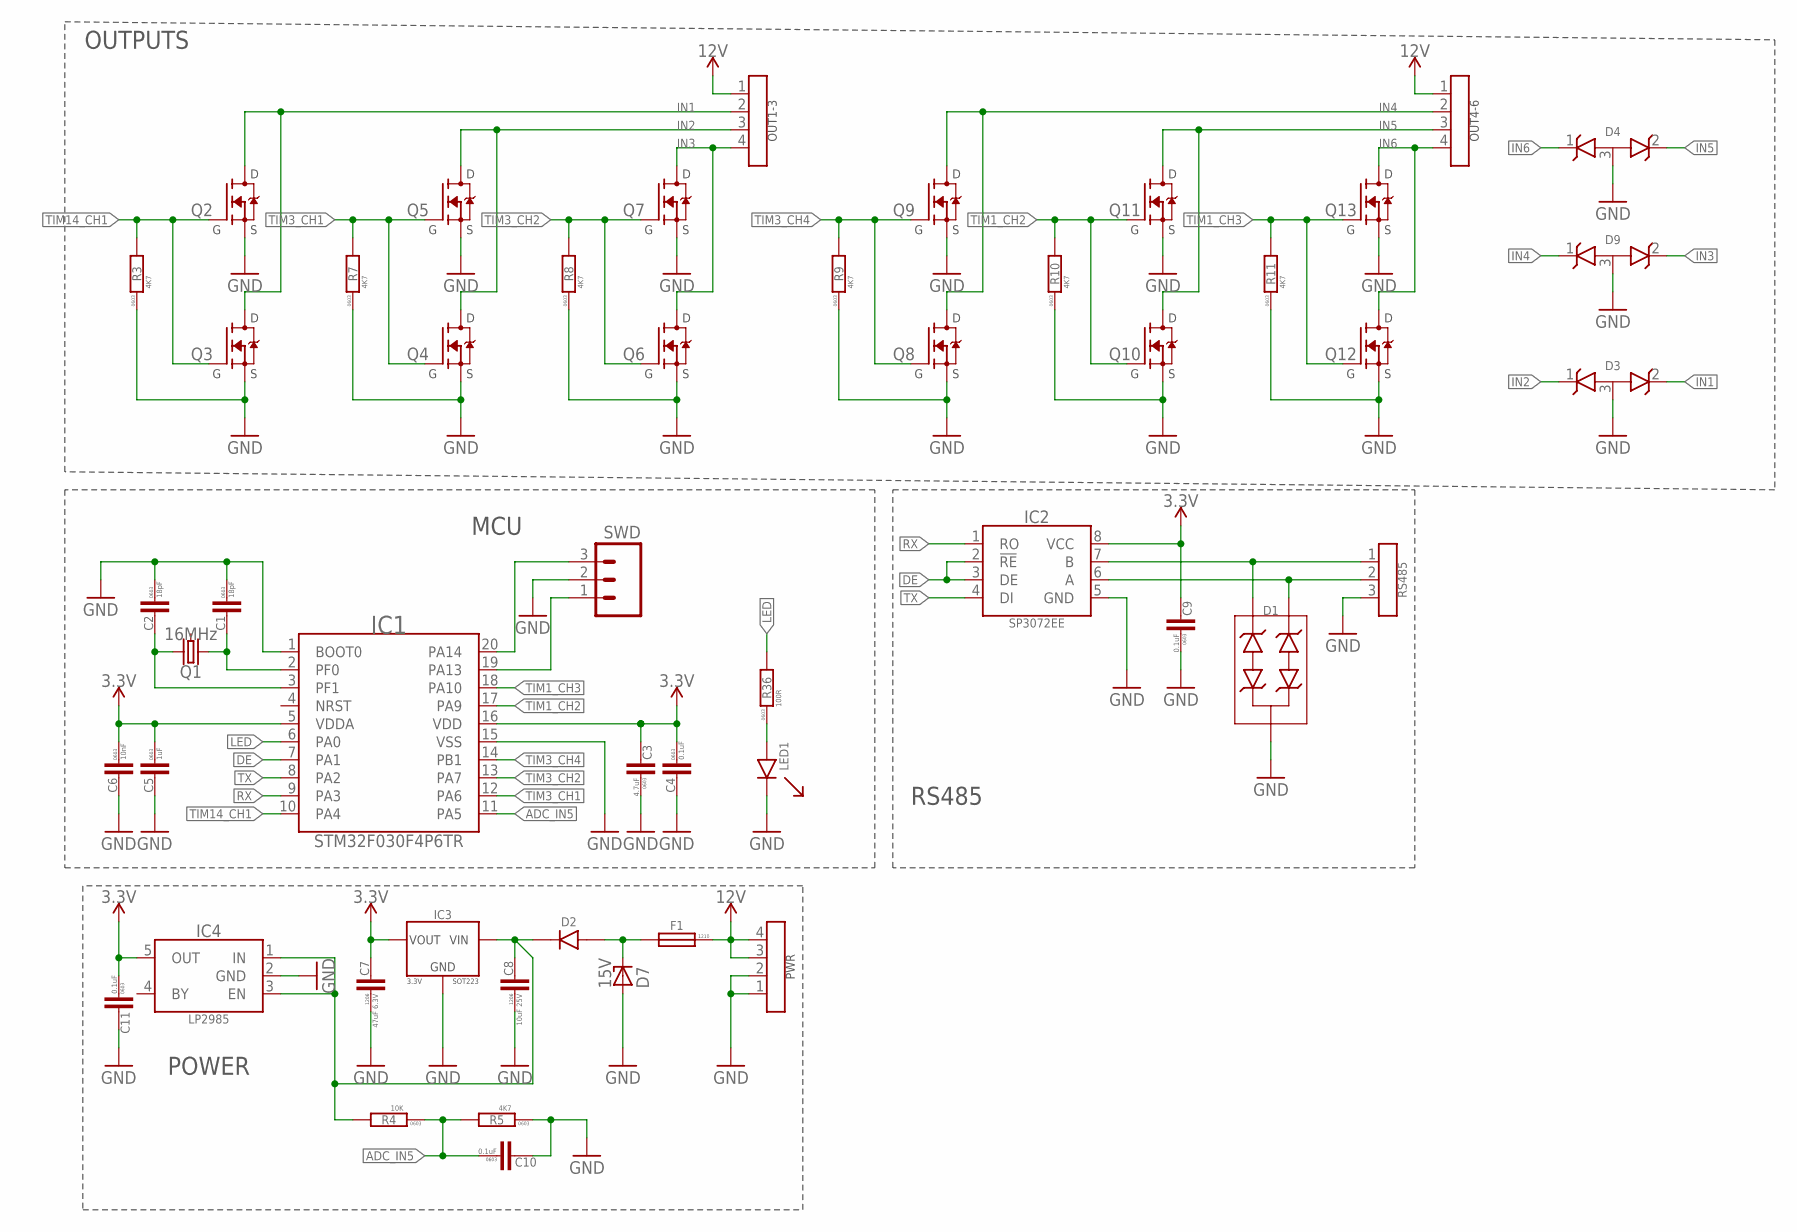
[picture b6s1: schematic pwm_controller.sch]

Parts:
C1, C2: 18pF; C0603
C3: 4.7uF; C0603
C4, C9, C10, C11: 0.1uF; C0603
C5: 1uF; C0603
C6: 10nF; C0603
C7: 47uF 6.3V; C1206
C8: 10uF 25V; C1206
D1: SM712; SOT23B-3
D2: MBR0520L-SOD123; SOD123
D3, D4, D9: SM12; SOT23B-3
D7: 15V; SOT23B-3; DIGIKEY# BZX84C15LT1GOSTR-ND
F1: FUSE-1210; F1210
IC1: STM32F030F4P6TR; TSSOP20
IC2: SP3072EESOIC8; SOIC8
IC3: LM1117-3.3-SOT223; SOT223@1
IC4: 3.3; SOT23-5L
LED1: LED-0603; 0603_LED
OUT1-3, OUT4-6: CON_4P-3.81; 3.81_RECEPTABLE_ANGLE_4P
PWR: CON_4P-3.81; 3.81_RECEPTABLE_ANGLE_4P
Q1: 16MHz; OSCILLATOR-3.2X2.5
Q2, Q5, Q7, Q9, Q11, Q13: IRLML2502-SOT23; SOT23B-3
Q3, Q4, Q6, Q8, Q10, Q12: STN3NF06L; SOT223@1
R3, R5, R7, R8, R9, R10, R11: 4K7; R0603
R4: 10K; R0603
R36: 100R; R0603
RS485: CON_3P-3.81; 3.81_RECEPTABLE_ANGLE_3P
SWD: M03PTH; 1X03

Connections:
A: D1.1 (C3), IC2.6 (A), RS485.2
ADC_IN5: C10.1, IC1.11 (PA5), R4.1, R5.2
B: D1.2 (C2), IC2.7 (B), RS485.1
DE: IC1.7 (PA1), IC2.2 (!RE), IC2.3 (DE)
GND: C1.1, C2.1, C3.1, C4.2, C5.2, C6.2, C7.P$1 (1), C8.P$1 (1), C9.1, C10.2, C11.2, D1.3, D3.3 (A), D4.3 (A), D7.1 (A), D9.3 (A), IC1.1 (BOOT0), IC1.15 (VSS), IC2.5 (GND), IC3.1 (GND), IC4.2 (GND), LED1.C, PWR.1, PWR.2, Q2.2 (S), Q3.3 (S), Q4.3 (S), Q5.2 (S), Q6.3 (S), Q7.2 (S), Q8.3 (S), Q9.2 (S), Q10.3 (S), Q11.2 (S), Q12.3 (S), Q13.2 (S), R3.1, R5.1, R7.1, R8.1, R9.1, R10.1, R11.1, RS485.3, SWD.2
IN1: D3.2 (C2), OUT1-3.2, Q2.3 (D), Q3.2 (D), Q3.4 (D)
IN2: D3.1 (C1), OUT1-3.3, Q4.2 (D), Q4.4 (D), Q5.3 (D)
IN3: D9.2 (C2), OUT1-3.4, Q6.2 (D), Q6.4 (D), Q7.3 (D)
IN4: D9.1 (C1), OUT4-6.2, Q8.2 (D), Q8.4 (D), Q9.3 (D)
IN5: D4.2 (C2), OUT4-6.3, Q10.2 (D), Q10.4 (D), Q11.3 (D)
IN6: D4.1 (C1), OUT4-6.4, Q12.2 (D), Q12.4 (D), Q13.3 (D)
LED: IC1.6 (PA0), R36.2
unnamed: C1.2, IC1.2 (PF0), Q1.1
unnamed: C8.P$2 (2), D2.C, IC3.3 (VIN), IC4.1 (IN), IC4.3 (EN), R4.2
unnamed: D2.A, D7.3 (C), F1.2
unnamed: C2.2, IC1.3 (PF1), Q1.3 (2)
unnamed: IC1.20 (PA14), SWD.3
unnamed: IC1.19 (PA13), SWD.1
unnamed: LED1.A, R36.1
RX: IC1.9 (PA3), IC2.1 (RO)
TIM1_CH2: IC1.17 (PA9), Q10.1 (G), Q11.1 (G), R10.2
TIM1_CH3: IC1.18 (PA10), Q12.1 (G), Q13.1 (G), R11.2
TIM3_CH1: IC1.12 (PA6), Q4.1 (G), Q5.1 (G), R7.2
TIM3_CH2: IC1.13 (PA7), Q6.1 (G), Q7.1 (G), R8.2
TIM3_CH4: IC1.14 (PB1), Q8.1 (G), Q9.1 (G), R9.2
TIM14_CH1: IC1.10 (PA4), Q2.1 (G), Q3.1 (G), R3.2
TX: IC1.8 (PA2), IC2.4 (DI)
VDD_3V3: C3.2, C4.1, C5.1, C6.1, C7.P$2 (2), C9.2, C11.1, IC1.5 (VDDA), IC1.16 (VDD), IC2.8 (VCC), IC3.2 (VOUT), IC3.4 (VOUT), IC4.5 (OUT)
VDD_12V: F1.1, OUT1-3.1, OUT4-6.1, PWR.3, PWR.4

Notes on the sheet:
RS485
POWER
OUTPUTS
MCU
